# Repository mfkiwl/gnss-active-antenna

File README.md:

<h1 align="center">
	GNSS Active Antenna Project
	<br>
</h1>

<p align="center">

</p>

<details>
    <summary><b>Summary</b></summary>
    <ol>
        <li>
            <a href="#overview">Overview</a>
        </li>
        <li>
            <a href="#repository-organization">Repository Organization</a>
        </li>
        <li>
            <a href="#license">License</a>
        </li>
        <li>
            <a href="#releases">Releases</a>
        </li>
        <li>
            <a href="#notes">Notes</a>
        </li>
        <li>
            <a href="#references">References</a>
        </li>
    </ol>
</details>

## Overview
​The GNSS Active Antenna project consists of developing an active antenna for the L1 band (1.565GHz), integrating a low noise amplifier (LNA) powered by 3.3V via picoblade connector.​ For the selection of components, the study project that appears in [[1]](#1) was used as a reference.
<!-- 

-->

<p align="center">

</p>

## Repository Organization
`hardware`: Main files of the hardware of the GNSS Active Antenna project.

`docs`: Technical documentation (including user guide and datasheet)

## License
This project is open-source under the following license: <a href="https://cern-ohl.web.cern.ch/home">CERN Open Hardware License v2.0</a> (CERN‑OHL‑P v2).  

## Releases

Releases are published after ensuring that the project itself do not have any major errors and after testing the PCB. Please refer to the **documentation** for more details.

## Notes
For more info about the SpaceLab, access our [GitHub](https://github.com/spacelab-ufsc/spacelab), [Linkedin](https://br.linkedin.com/company/spacelab-ufsc) or our [website](https://spacelab.ufsc.br/en/home/).

## References
<a id="1">[1]</a> Sandro Klarer, "Does a LNA (Low Noise Amplifier) improve my GNSS Position Accuracy," in <i>NOSER ENGINEERING</i>, 2025, available at <a href="https://www.noser.com/techblog/does-a-lna-low-noise-amplifier-improve-my-gnss-position-accuracy/"> this link</a>.

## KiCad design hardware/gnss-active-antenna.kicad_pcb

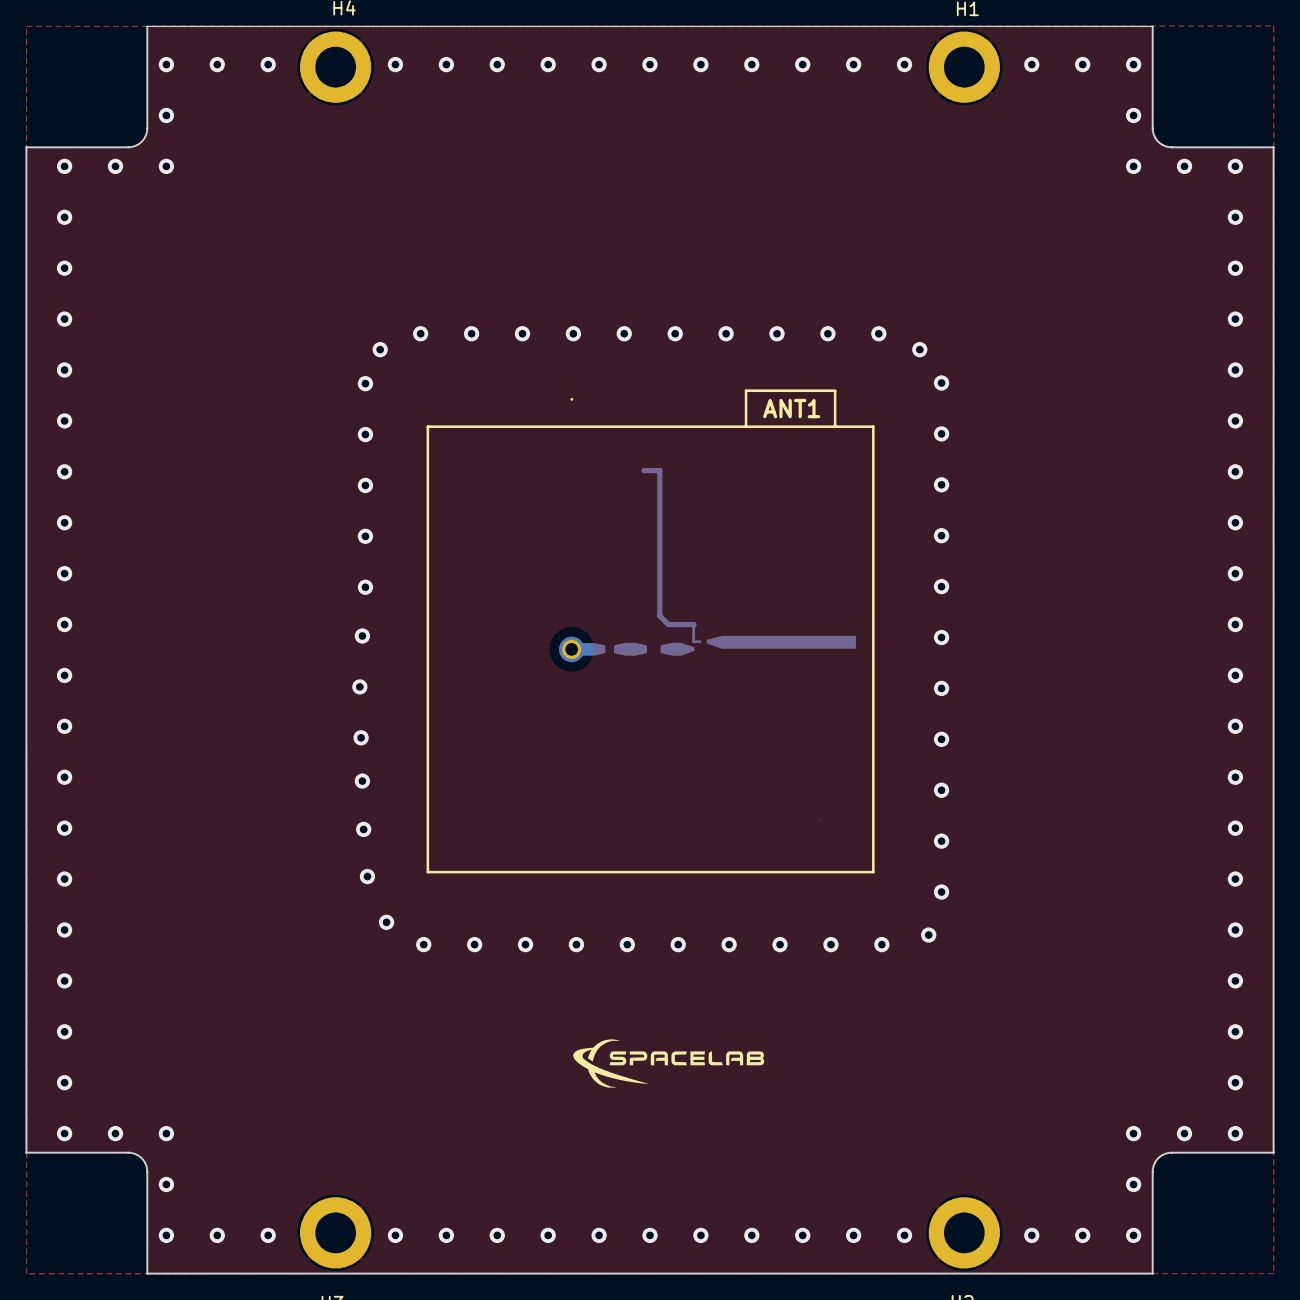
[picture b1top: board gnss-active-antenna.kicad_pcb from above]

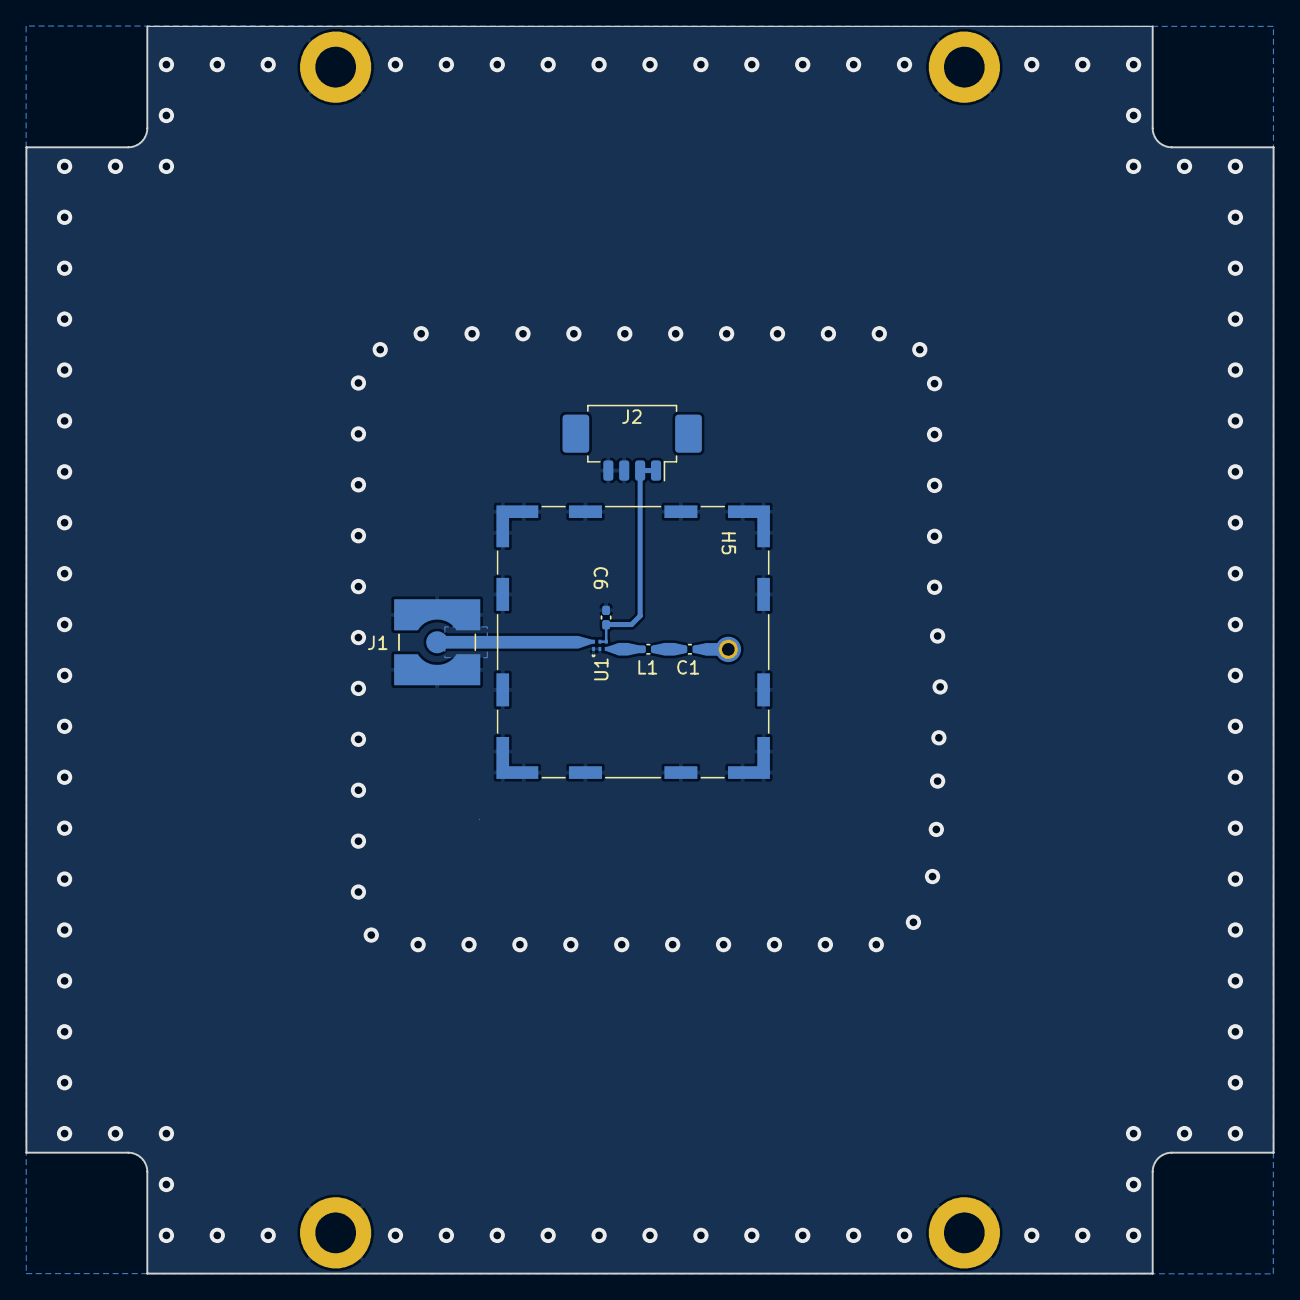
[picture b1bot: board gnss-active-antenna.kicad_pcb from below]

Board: 2 copper layers, 98.0 x 98.0 mm, 12 parts (7 on the bottom side), 6 nets.

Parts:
ANT1: GGBTP.35.3.A.40; GGBTP353A40
C1: 24pF; C_0402_1005Metric_Pad0.74x0.62mm_HandSolder
C6: 33 nF; C_0402_1005Metric_Pad0.74x0.62mm_HandSolder
H1, H2, H3, H4: MountingHole_Pad; MountingHole_3.2mm_M3_DIN965_Pad
H5: WE-SHC_ONE-PIECE; Wuerth_36103205_20x20mm
J1: CONMCX002-SMD; LINX_CONMCX002-SMD
J2: Conn_01x04_Pin; Molex_PicoBlade_53261-0471_1x04-1MP_P1.25mm_Horizontal
L1: 6.2 nH; C_0402_1005Metric_Pad0.74x0.62mm_HandSolder
U1: MAX2659ELT+T; 21-0147-L611

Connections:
3V3: C6.1, J2.1, J2.2, U1.4 (VCC), U1.5 (*SHDN)
GND: C6.2, H1.1, H2.1, H3.1, H4.1, H5.1, J1.S1, J1.S2, J2.3, J2.4, U1.1 (GND), U1.2 (GND)
unnamed: C1.2, L1.1
unnamed: L1.2, U1.3 (RFIN)
ant: ANT1.1, C1.1
rfout: J1.1, U1.6 (RFOUT)

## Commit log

2025-04-21 main: README.md: Project overview added
2025-04-21 main: README.md: Added right pictures location
2025-04-21 main: docs folder added
2025-04-21 main: pictures: antenna pictures cropped
2025-04-21 main: hardware folder with project added
2025-04-21 main: README.md: components reference cited
2025-04-21 main: README.md: link to CERN Licence added
2025-05-26 main: .gitignore file updated
2025-05-26 main: hardware: schematic update
2025-05-26 main: hardware: manufacture files updated and added
2025-05-30 main: hardware: The bias-tee design was removed to make the first design simpler
2025-05-30 main: hardware: New files for production added
